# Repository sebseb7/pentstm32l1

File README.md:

# PentSTM32-l1 

a small template project to use with the stm32l1xx

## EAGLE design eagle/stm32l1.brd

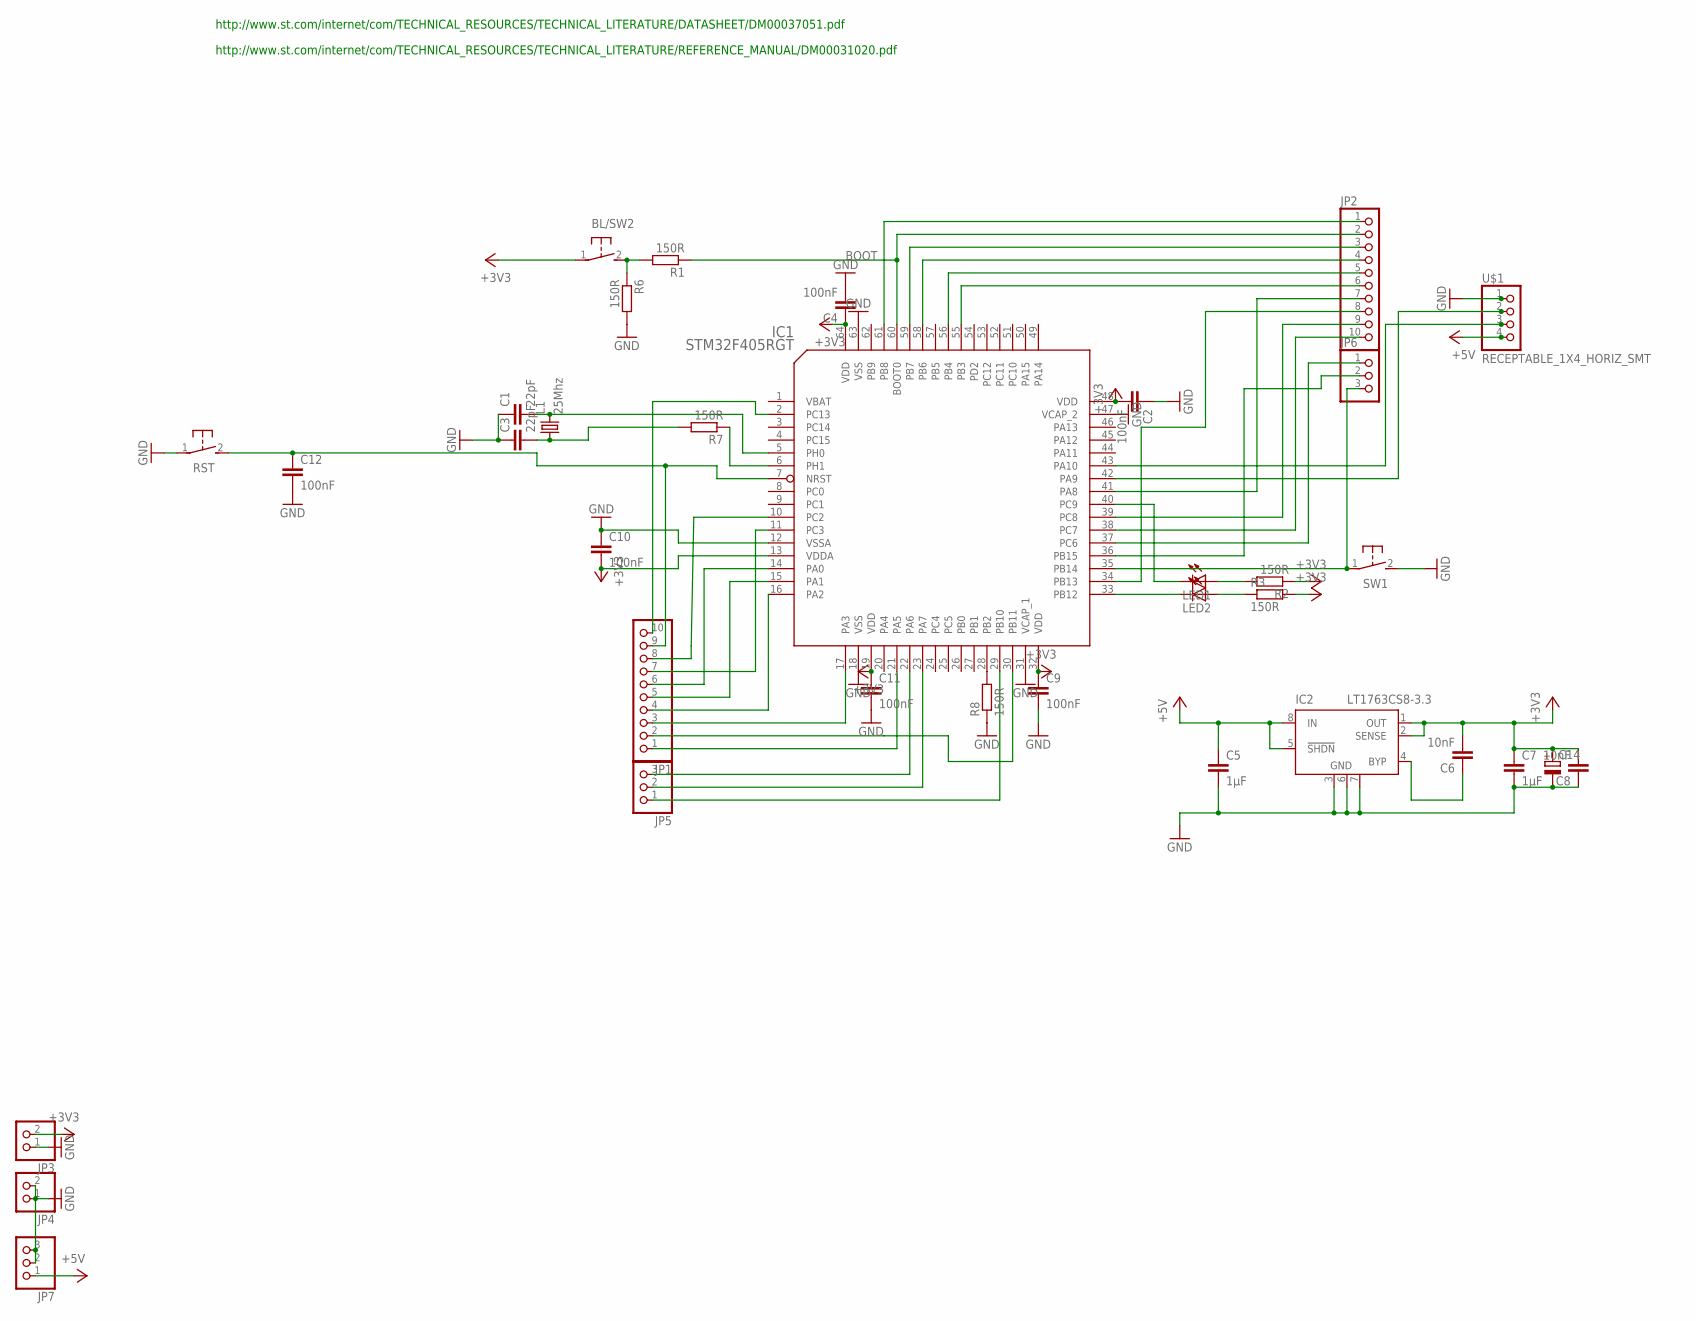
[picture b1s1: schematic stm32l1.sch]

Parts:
BL/SW2: SWITCH_MCTAEF
C1, C3: 22pF; C0402
C2, C4, C9, C10, C11, C12: 100nF; C0402
C5, C7: 1µF; 0805
C6, C8: 10nF; C0402
C14: CPOL-EUSMCA; SMC_A
IC1: STM32F405RGT; LQFP64
IC2: LT1763CS8-3.3; SOIC8
JP1, JP2: PINHD-1X10_2.54; 1X10
JP3, JP4: PINHD-1X02_2.54; 1X02
JP5, JP6, JP7: PINHD-1X03_2.54; 1X03
L1: 25Mhz; X22
LED1, LED2: LEDCHIPLED_0805; CHIPLED_0805
R1, R2, R3, R6, R7, R8: 150R; R0402
RST: SWITCH_MCTAEF
SW1: SWITCH_MCTAEF
U$1: RECEPTABLE_1X4_HORIZ_SMT

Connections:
+3V3: BL/SW2.1, C2.2, C4.1, C6.2, C7.1, C8.2, C9.1, C10.2, C11.1, C14.+, IC1.13 (VDDA), IC1.19 (VDD), IC1.32 (VDD), IC1.48 (VDD), IC1.64 (VDD), IC2.1 (OUT), IC2.2 (SENSE), JP3.2, R2.1, R3.2
+5V: C5.1, IC2.5 (!SHDN), IC2.8 (IN), JP7.1, U$1.4, U$1.4@1 (4)
A0: IC1.14 (PA0), JP1.6
A3: IC1.17 (PA3), JP1.3
A4: IC1.30 (PB11), JP1.2
A5: IC1.21 (PA5), JP1.1
A6: IC1.22 (PA6), JP5.3
A8: IC1.41 (PA8), JP2.7
B4: IC1.56 (PB4), JP2.5
B6: IC1.58 (PB6), JP2.4
B7: IC1.59 (PB7), JP2.3
B8: IC1.61 (PB8), JP2.1
B10: IC1.29 (PB10), JP5.1
B14: IC1.35 (PB14), JP6.3, SW1.1
B15: IC1.36 (PB15), JP6.2
BOOT: IC1.60 (BOOT0), JP2.2, R1.1
C2: IC1.10 (PC2), JP1.8
C3: IC1.11 (PC3), JP1.7
C6: IC1.37 (PC6), JP6.1
C7: IC1.38 (PC7), JP2.10
C8: IC1.39 (PC8), JP2.9
C12: IC1.34 (PB13), JP2.8
ETH_MDIO: IC1.16 (PA2), JP1.4
ETH_RMII_CRS_DV: IC1.23 (PA7), JP5.2
ETH_RMII_REF_CLK: IC1.15 (PA1), JP1.5
ETH_RMII_TXD0: IC1.33 (PB12), LED2.C
ETH_RMII_TXD1: IC1.40 (PC9), LED1.C
GND: C1.1, C2.1, C3.1, C4.2, C5.2, C7.2, C8.1, C9.2, C10.1, C11.2, C12.2, C14.-, IC1.12 (VSSA), IC1.18 (VSS), IC1.31 (VCAP_1), IC1.47 (VCAP_2), IC1.63 (VSS), IC2.3 (GND), IC2.6 (GND), IC2.7 (GND), JP3.1, JP4.1, JP4.2, JP7.2, JP7.3, R6.2, R8.1, RST.1, SW1.2, U$1.1, U$1.1@1 (1)
unnamed: IC1.42 (PA9), U$1.2, U$1.2@1 (2)
unnamed: IC1.43 (PA10), U$1.3, U$1.3@1 (3)
unnamed: IC1.6 (PH1), R7.1
unnamed: C1.2, IC1.5 (PH0), L1.3 (2)
unnamed: C12.1, IC1.7 (NRST), JP1.9, RST.2
unnamed: BL/SW2.2, R1.2, R6.1
unnamed: C3.2, L1.1, R7.2
unnamed: IC1.28 (PB2), R8.2
unnamed: C6.1, IC2.4 (BYP)
unnamed: LED1.A, R2.2
unnamed: LED2.A, R3.1
PB3: IC1.55 (PB3), JP2.6
PC13: IC1.2 (PC13), JP1.10
VBAT: IC1.1 (VBAT)

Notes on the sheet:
http://www.st.com/internet/com/TECHNICAL_RESOURCES/TECHNICAL_LITERATURE/REFERENCE_MANUAL/DM00031020.pdf
http://www.st.com/internet/com/TECHNICAL_RESOURCES/TECHNICAL_LITERATURE/DATASHEET/DM00037051.pdf

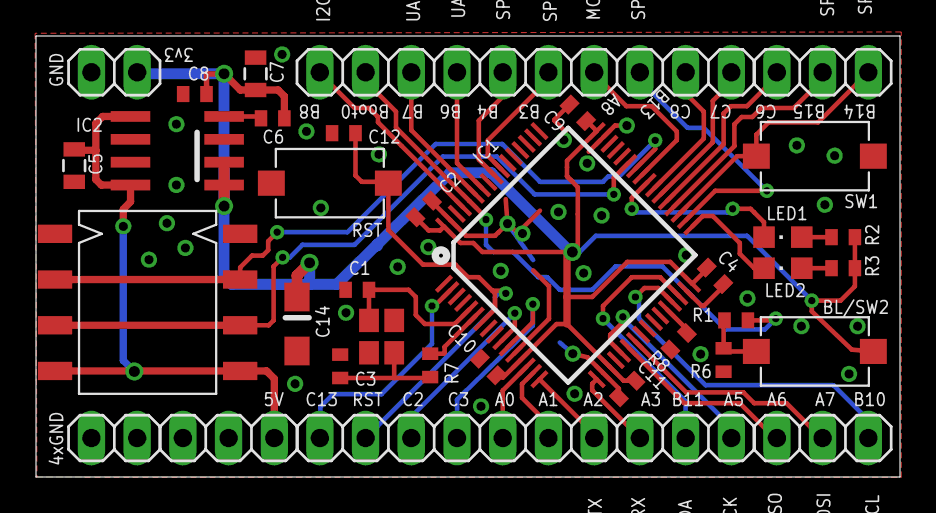
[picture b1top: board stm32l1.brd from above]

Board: 2 copper layers, 48.0 x 24.5 mm, 35 parts (0 on the bottom side), 41 nets.

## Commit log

2012-09-20 init
2012-09-21 added support for device id 0x416 (stm32l151)
2012-09-21 synced stm32flash upstream
2012-09-21 switched from 8mhz to 12mhz crystal
2012-09-21 printf
2012-09-21 memcpy
2012-09-21 added stm32l1 drivers and blinking example
2012-09-21 eagle files
2012-09-21 misc
2012-09-21 compile warnings
2012-09-21 ordered
2012-09-21 fix hole
2012-09-21 fix hole
    Conflicts:
    eagle/stm32l1.brd
